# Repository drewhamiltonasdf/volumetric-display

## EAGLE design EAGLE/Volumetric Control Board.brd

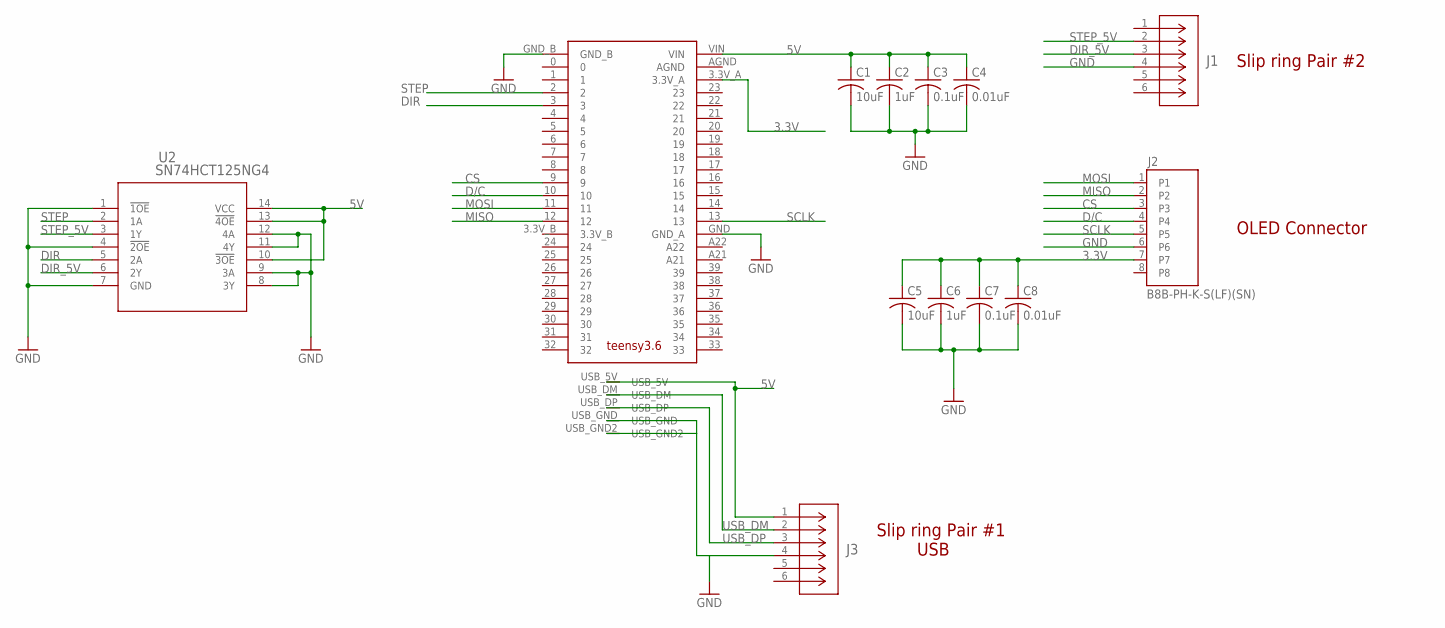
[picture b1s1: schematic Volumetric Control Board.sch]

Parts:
C1, C5: 10uF; C1206
C2, C6: 1uF; C1206
C3, C7: 0.1uF; C1206
C4, C8: 0.01uF; C1206
J1, J3: B6B-PH-K-S(LF)(SN); CONN_B6B-PH-K-S_JST
J2: B8B-PH-K-S(LF)(SN); JST_B8B-PH-K-S(LF)(SN)
U2: SN74HCT125NG4; N14_TEX
U$1: TEENSY3.6

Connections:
3.3V: C5.1, C6.1, C7.1, C8.1, J2.7, U$1.3.3V_A
5V: C1.1, C2.1, C3.1, C4.1, J3.1, U2.10 (!3OE), U2.13 (!4OE), U2.14 (VCC), U$1.USB_5V, U$1.VIN
CS: J2.3, U$1.9
D/C: J2.4, U$1.10
DIR: U2.5 (2A), U$1.3
DIR_5V: J1.3, U2.6 (2Y)
GND: C1.2, C2.2, C3.2, C4.2, C5.2, C6.2, C7.2, C8.2, J1.4, J2.6, J3.4, U2.1 (!1OE), U2.4 (!2OE), U2.7 (GND), U2.8 (3Y), U2.9 (3A), U2.11 (4Y), U2.12 (4A), U$1.GND (GND_A), U$1.GND_B, U$1.USB_GND, U$1.USB_GND2
MISO: J2.2, U$1.12
MOSI: J2.1, U$1.11
SCLK: J2.5, U$1.13
STEP: U2.2 (1A), U$1.2
STEP_5V: J1.2, U2.3 (1Y)
USB_DM: J3.2, U$1.USB_DM
USB_DP: J3.3, U$1.USB_DP

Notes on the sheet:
Slip ring Pair #1 USB
Slip ring Pair #2
OLED Connector

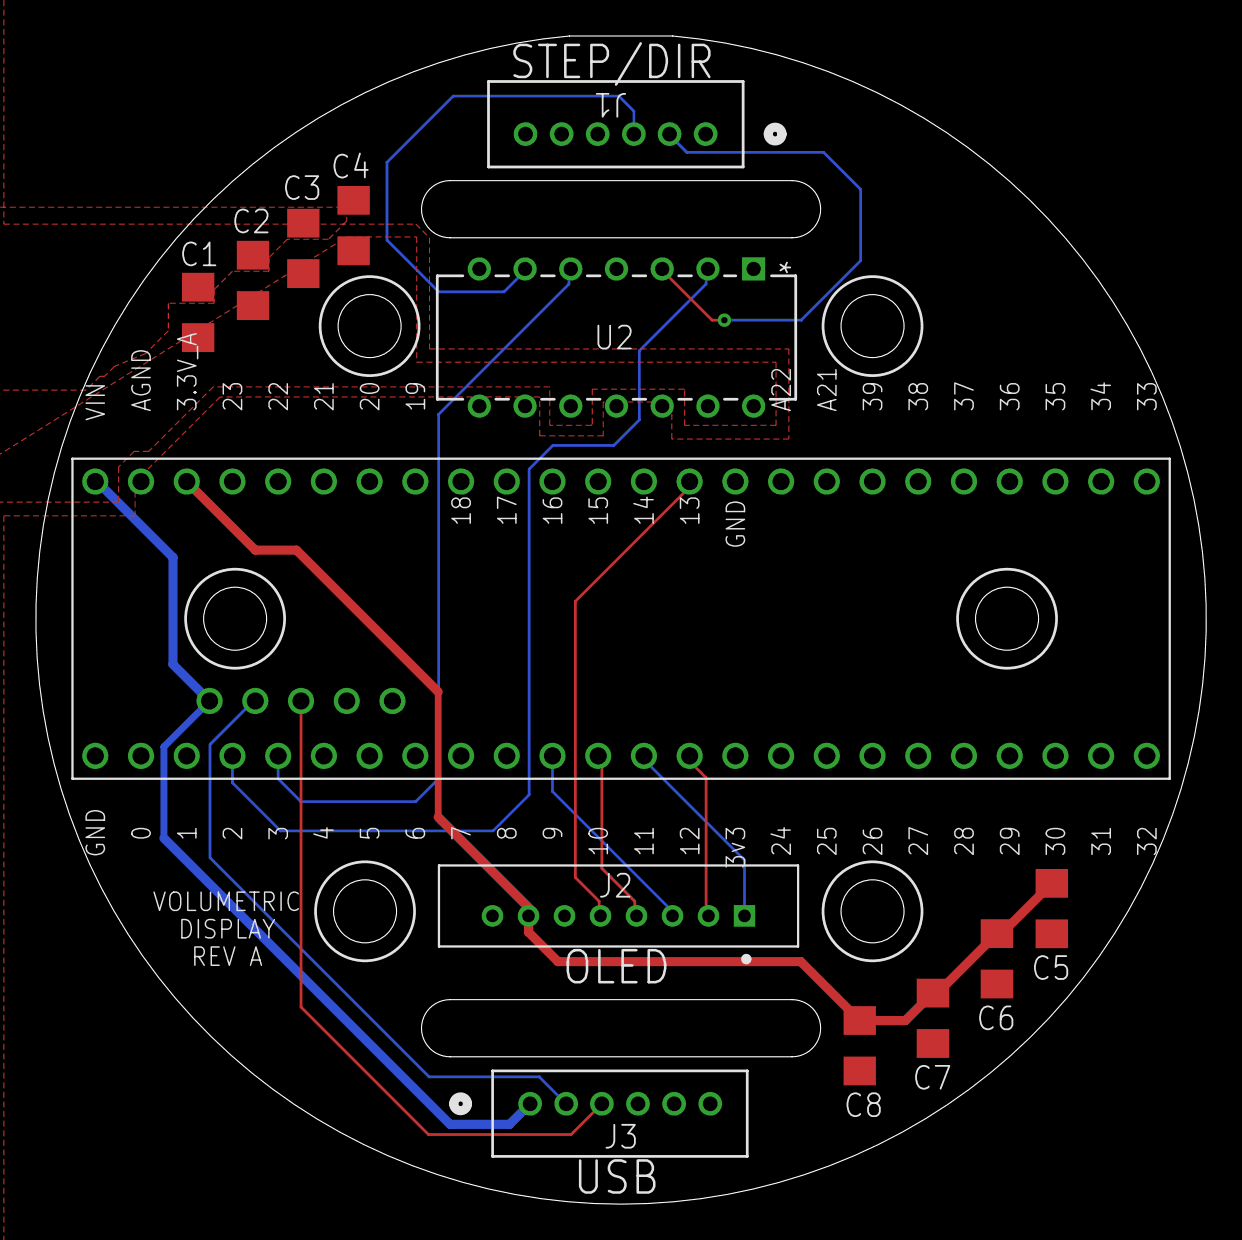
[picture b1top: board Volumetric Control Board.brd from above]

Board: 2 copper layers, 65.0 x 64.9 mm, 13 parts (0 on the bottom side), 14 nets.

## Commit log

2021-10-19 First quick holder for display
2021-10-20 Rev2 holder
2021-10-21 REV3 widened opening for OLED and moved holes for header pins
2021-10-31 Solidworks Assembly 1st draft and EAGLE Board started
2021-11-02 Fiddled with code after using new level translator to get max speeds
2021-11-02 Added 3d file for the level shifter
2021-11-02 EAGLE stuff started
2021-11-06 adsf
2021-11-14 Quick sketch with plane-line segment intersection algorithm
2021-11-20 Semi-final 3D model for first prototype
2021-11-30 First few arduino sketches for REV A functional device

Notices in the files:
parts and their libraries:
COPYRIGHT: Copyright (C) 2021 Ultra Librarian. All rights reserved.
